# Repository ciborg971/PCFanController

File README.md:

# PCFanController

A completly ~~overkill~~ sound and smart fan controller able to :
- use RP2040
- have USB-C
- 3x NTC 10K sensor (temperature sensor)
- 2x separated buses for DS18B20 (more temperature sensor)
- 2x separated WS2812 buses (RGB led)
- E-Ink display support
- 7x PWM fan support with tachymeter reading
- 2x 12 volt PWM output (Up to 20A per port)
- 2.5 inch hdd dimension (100 x 50 mm)
- M2 hole (between hole 85.25 x 38 mm)

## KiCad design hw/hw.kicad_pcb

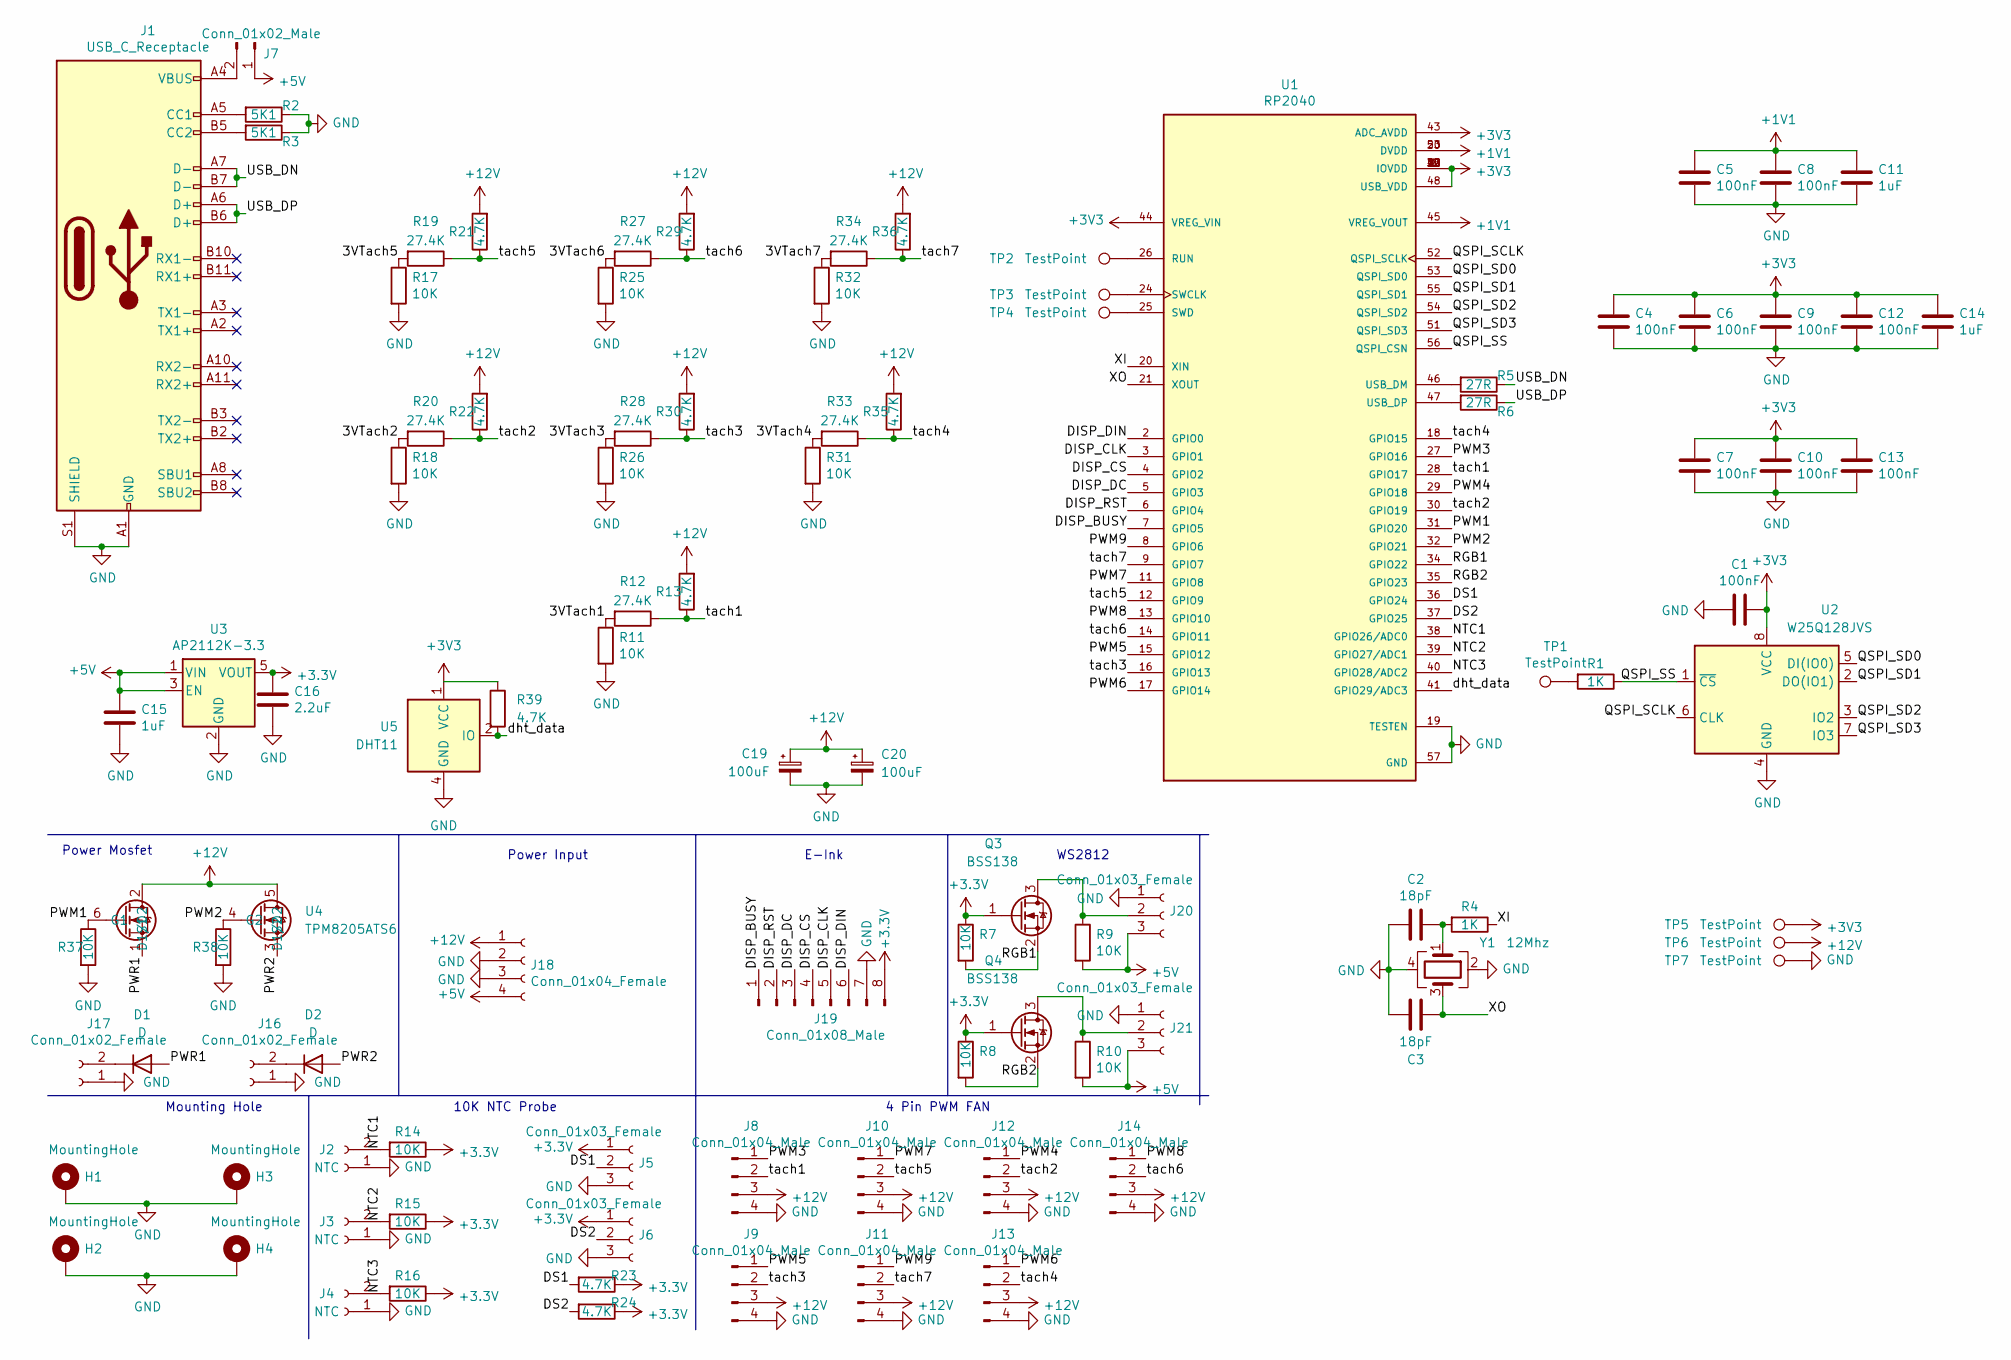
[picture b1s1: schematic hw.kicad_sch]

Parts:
C1, C4, C5, C6, C7, C8, C9, C10, C12, C13: 100nF; C_0402_1005Metric
C2, C3: 18pF; C_0402_1005Metric
C11, C14, C15: 1uF; C_0402_1005Metric
C16: 2.2uF; C_0402_1005Metric
C19, C20: 100uF; CP_EIA-7343-43_Kemet-X; LCSC C7230
D1, D2: D; D_0805_2012Metric
H1, H2, H3, H4: MountingHole; MountingHole_2.2mm_M2_ISO7380_Pad
J1: USB_C_Receptacle; USB_C_Receptacle_Amphenol_12401610E4-2A
J2, J3, J4: NTC; PinHeader_1x02_P2.54mm_Vertical
J5, J6, J20, J21: Conn_01x03_Female; PinHeader_1x03_P2.54mm_Vertical
J7: Conn_01x02_Male; PinSocket_1x02_P2.54mm_Vertical
J8, J9, J10, J11, J12, J13, J14: Conn_01x04_Male; PinHeader_1x04_P2.54mm_Vertical; LCSC C240840
J16, J17: Conn_01x02_Female; PinHeader_1x02_P2.54mm_Vertical
J18: Conn_01x04_Female; PinSocket_1x04_P2.54mm_Vertical
J19: Conn_01x08_Male; PinHeader_1x08_P2.54mm_Vertical
Q3, Q4: BSS138; SOT-23
R1, R4: 1K; R_0402_1005Metric
R2, R3: 5K1; R_0402_1005Metric
R5, R6: 27R; R_0402_1005Metric
R7, R8, R9, R10, R11, R14, R15, R16, R17, R18, R25, R26, R31, R32, R37, R38: 10K; R_0402_1005Metric
R12, R19, R20, R27, R28, R33, R34: 27.4K; R_0402_1005Metric
R13, R21, R22, R23, R24, R29, R30, R35, R36, R39: 4.7K; R_0402_1005Metric
TP1, TP2, TP3, TP4, TP5, TP6, TP7: TestPoint; TestPoint_Pad_D1.5mm
U1: RP2040; QFN40P700X700X90-57N; PARTREV 1.6.1; LCSC C2040
U2: W25Q128JVS; SOIC-8_5.23x5.23mm_P1.27mm; LCSC C82317
U3: AP2112K-3.3; SOT-23-5
U4: TPM8205ATS6; TSOT-23-6
U5: DHT11; Aosong_DHT11_5.5x12.0_P2.54mm
Y1: 12Mhz; Crystal_SMD_3225-4Pin_3.2x2.5mm; LCSC C124304

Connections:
+1V1: C5.1, C8.1, C11.1, U1.23 (DVDD), U1.45 (VREG_VOUT), U1.50 (DVDD)
+5V: C15.1, J7.1, J18.4, J20.3, J21.3, R9.2, R10.2, U3.1 (VIN), U3.3 (EN)
+12V: C19.1, C20.1, J8.3, J9.3, J10.3, J11.3, J12.3, J13.3, J14.3, J18.1, R13.2, R21.2, R22.2, R29.2, R30.2, R35.2, R36.2, TP6.1, U4.2 (D1/D2), U4.5 (D1/D2)
/3VTach1: R11.1, R12.2
/3VTach2: R18.1, R20.2
/3VTach3: R26.1, R28.2
/3VTach4: R31.1, R33.2
/3VTach5: R17.1, R19.2
/3VTach6: R25.1, R27.2
/3VTach7: R32.1, R34.2
/DISP_BUSY: J19.1, U1.7 (GPIO5)
/DISP_CLK: J19.5, U1.3 (GPIO1)
/DISP_CS: J19.4, U1.4 (GPIO2)
/DISP_DC: J19.3, U1.5 (GPIO3)
/DISP_DIN: J19.6, U1.2 (GPIO0)
/DISP_RST: J19.2, U1.6 (GPIO4)
/DS1: J5.2, R23.2, U1.36 (GPIO24)
/DS2: J6.2, R24.2, U1.37 (GPIO25)
/NTC1: J2.2, R14.2, U1.38 (GPIO26/ADC0)
/NTC2: J3.2, R15.2, U1.39 (GPIO27/ADC1)
/NTC3: J4.2, R16.2, U1.40 (GPIO28/ADC2)
/PWM1: R37.1, U1.31 (GPIO20), U4.6 (G1)
/PWM2: R38.1, U1.32 (GPIO21), U4.4 (G2)
/PWM3: J8.1, U1.27 (GPIO16)
/PWM4: J12.1, U1.29 (GPIO18)
/PWM5: J9.1, U1.15 (GPIO12)
/PWM6: J13.1, U1.17 (GPIO14)
/PWM7: J10.1, U1.11 (GPIO8)
/PWM8: J14.1, U1.13 (GPIO10)
/PWM9: J11.1, U1.8 (GPIO6)
/PWR1: D1.2 (A), U4.1 (S1)
/PWR2: D2.2 (A), U4.3 (S2)
/QSPI_SCLK: U1.52 (QSPI_SCLK), U2.6 (CLK)
/QSPI_SD0: U1.53 (QSPI_SD0), U2.5 (DI(IO0))
/QSPI_SD1: U1.55 (QSPI_SD1), U2.2 (DO(IO1))
/QSPI_SD2: U1.54 (QSPI_SD2), U2.3 (IO2)
/QSPI_SD3: U1.51 (QSPI_SD3), U2.7 (IO3)
/QSPI_SS: R1.1, U1.56 (QSPI_CSN), U2.1 (~CS)
/RGB1: Q3.2 (S), R7.2, U1.34 (GPIO22)
/RGB2: Q4.2 (S), R8.2, U1.35 (GPIO23)
/USB_DN: J1.A7 (D-), J1.B7 (D-), R5.1
/USB_DP: J1.A6 (D+), J1.B6 (D+), R6.1
/XI: R4.1, U1.20 (XIN)
/XO: C3.1, U1.21 (XOUT), Y1.3
/dht_data: R39.2, U1.41 (GPIO29/ADC3), U5.2 (IO)
/tach1: J8.2, R12.1, R13.1, U1.28 (GPIO17)
/tach2: J12.2, R20.1, R22.1, U1.30 (GPIO19)
/tach3: J9.2, R28.1, R30.1, U1.16 (GPIO13)
/tach4: J13.2, R33.1, R35.1, U1.18 (GPIO15)
/tach5: J10.2, R19.1, R21.1, U1.12 (GPIO9)
/tach6: J14.2, R27.1, R29.1, U1.14 (GPIO11)
/tach7: J11.2, R34.1, R36.1, U1.9 (GPIO7)
GND: C1.2, C2.2, C3.2, C4.2, C5.2, C6.2, C7.2, C8.2, C9.2, C10.2, C11.2, C12.2, C13.2, C14.2, C15.2, C16.2, C19.2, C20.2, H1.1, H2.1, H3.1, H4.1, J1.A1 (GND), J1.A12 (GND), J1.B1 (GND), J1.B12 (GND), J1.S1 (SHIELD), J2.1, J3.1, J4.1, J5.3, J6.3, J8.4, J9.4, J10.4, J11.4, J12.4, J13.4, J14.4, J16.1, J17.1, J18.2, J18.3, J19.7, J20.1, J21.1, R2.1, R3.1, R11.2, R17.2, R18.2, R25.2, R26.2, R31.2, R32.2, R37.2, R38.2, TP7.1, U1.19 (TESTEN), U1.57 (GND), U2.4 (GND), U3.2 (GND), U5.4 (GND), Y1.2, Y1.4
unnamed: C2.1, R4.2, Y1.1
unnamed: D1.1 (K), J17.2
unnamed: D2.1 (K), J16.2
unnamed: J1.A4 (VBUS), J1.A9 (VBUS), J1.B4 (VBUS), J1.B9 (VBUS), J7.2
unnamed: J1.A5 (CC1), R2.2
unnamed: J1.B5 (CC2), R3.2
unnamed: J20.2, Q3.3 (D), R9.1
unnamed: J21.2, Q4.3 (D), R10.1
unnamed: R1.2, TP1.1
unnamed: R5.2, U1.46 (USB_DM)
unnamed: R6.2, U1.47 (USB_DP)
unnamed: TP2.1, U1.26 (RUN)
unnamed: TP3.1, U1.24 (SWCLK)
unnamed: TP4.1, U1.25 (SWD)

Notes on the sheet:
Mounting Hole
Power Mosfet
10K NTC Probe
WS2812
Power Input
4 Pin PWM FAN
E-Ink

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
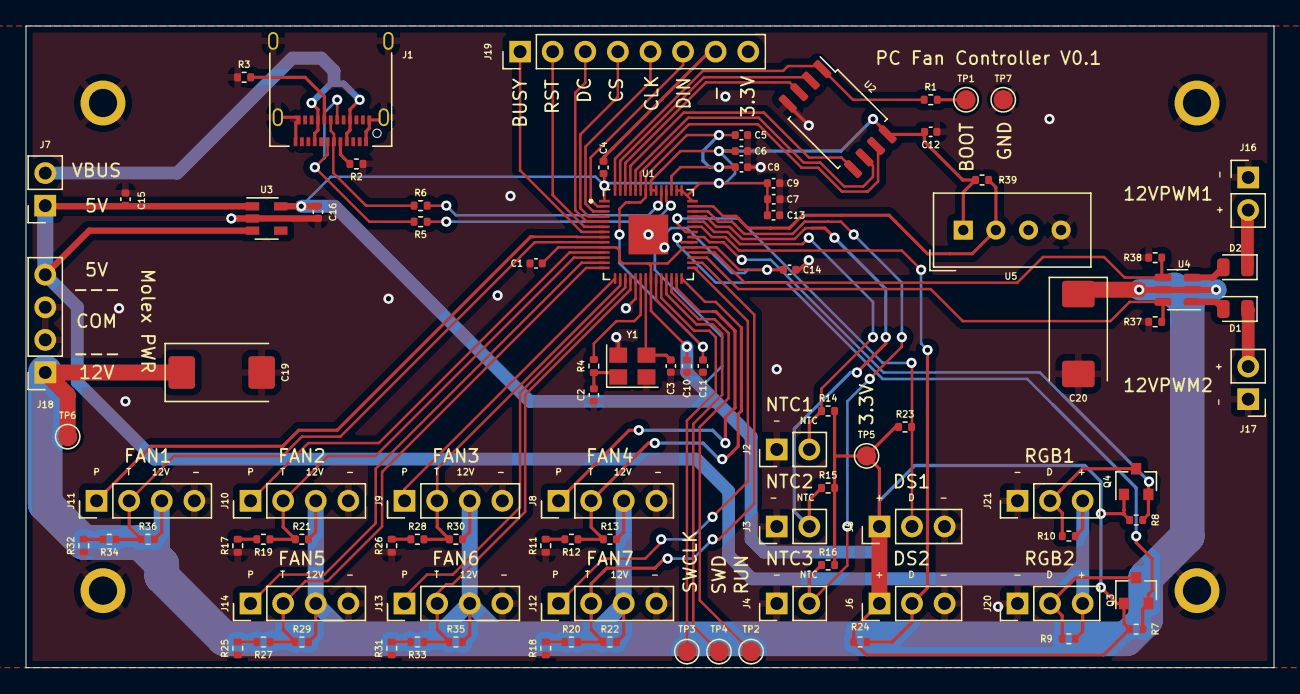
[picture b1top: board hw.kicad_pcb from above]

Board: 2 copper layers, 97.2 x 50.0 mm, 98 parts (0 on the bottom side), 68 nets.

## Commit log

2022-09-30 schematic + placement of most component
2022-10-02 doc 4 pin fan schematic
2022-10-12 rooting progress + update readme + change power transistor
2022-11-01 add label, fix 12 v track width, connect everything
2022-11-01 reduce size of the board and update readme
2022-11-02 add dht11/22 support
    hwmon have humidity support and... i have some dht laying aroung ...
